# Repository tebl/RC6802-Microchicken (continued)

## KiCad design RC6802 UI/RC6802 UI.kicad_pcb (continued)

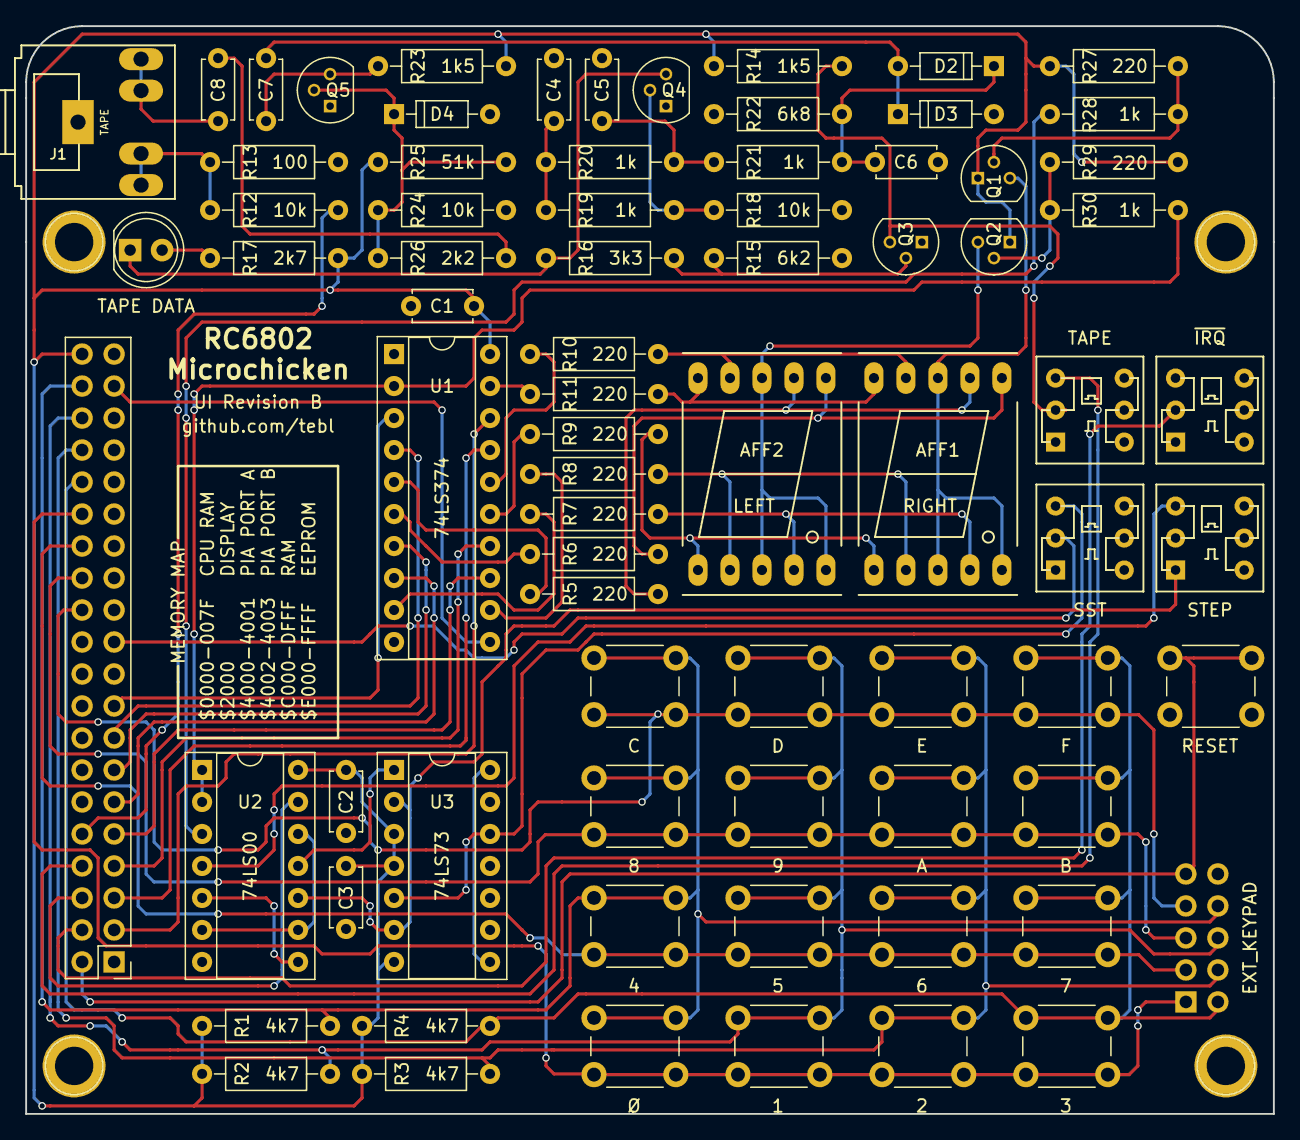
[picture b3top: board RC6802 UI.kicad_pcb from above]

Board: 2 copper layers, 99.1 x 86.4 mm, 80 parts (1 on the bottom side), 66 nets.

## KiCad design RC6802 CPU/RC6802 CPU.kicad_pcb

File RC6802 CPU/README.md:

# RC6802 Microchicken

One of my most enjoyable reads the past year has been "22 micro-computer projects - to build, learn and learn" by Daniel L. Metzger, the Microchicken-computer is described in detail within it and so I sought to build one myself. The computer has been designed as a set of smaller modules, for an overall description a listing of the available modules - see the main project [README](https://github.com/tebl/RC6802-Microchicken)!

## CPU
The CPU module has been designed to stack with the User Interface-module, doing it this way the overall project stays within manageable PCB-costs and should be buildable for anyone with a reasonable set of tools available. An assembled version of the CPU-module by itself as well as a version stacked underneath the User Interface module can be seen below.

The CPU board is actually a complete SBC (Single Board Computer) by itself, meaning that it can be used either standalone though you'd probably need to add some sort of additional hardware in order to see anything actually running. I hope to build more modules that can be used with it other than the standard User Interface. 

Some of the ICs however have been changed out with components that should be easier to source for a lot less money. For those that find themselves wondering why there are ICs with more capacity (RAM/ROM) than is actually available to the system, it's simply because they were cheaper than the smaller capacity variants and I didn't want to lay claim to more of the address space than what the original computer calls for (8K for each).

## Jumpers
| Reference | Position | Description                                        |
| --------- | -------- | -------------------------------------------------- |
| RAM_EN    | 1-2 *    | Enable on-chip 128 bytes of memory on 6802 CPU     |
|           | 2-3      | Disable on-chip memory or jumper if using 6808 CPU |
| RAM_SEL   | 1-2 *    | 8K of static RAM on addresses $C000-$DFFF          |
|           | 2-3      | 8k of static RAM on addresses $0000-$1FFF          |
| LED_EN    | 1-2 *    | Enable status LEDs                                 |
|           | 2-3      | Disable status LEDs                                |
| A14, A13  | 1-2 **   | EEPROM 8K window selection (sets line HIGH)        |
|           | 2-3 **   | EEPROM 8K window selection (sets line LOW)         |

*) Marks the default jumpered positions for a standalone RC6802 system with 6802 CPU installed.
**) A14 and A13 must be jumpered when using 28C256 EEPROM, leave unjumpered when using the lower capacity 28C64 EEPROM instead.

# Schematic
The supplied KiCad files should be sufficient as both a schematic and as a starting point for ordering PCBs (basically you could just zip the contents of the export folder and upload that on a fabrication site), the schematic is also available in [PDF-format](https://github.com/tebl/RC6802-Microchicken/raw/master/RC6802%20CPU/export/RC6802%20CPU.pdf) so that you print it out and hang it on your office wall, excellent conversation starter at any technology-oriented business worth working at (or so I keep telling myself)!

If you require more assistance, there is also a separate [Troubleshooting](https://github.com/tebl/RC6802-Microchicken/blob/master/Troubleshooting.md) guide as part of the supplied documentation. Also make sure to have a read through the [Manual](https://github.com/tebl/RC6802-Microchicken/blob/master/Manual.md) to see if it's a *feature* instead! Some of these documents may not actually exist at the time of clicking on them.

# BOM
This is the part list as it stands now, most should be easy to get a hold of from your local electronic component shop though you might have to consider other sources depending on the quality of your local vendor. Values in parenthesis are optional components that might not be needed (status LEDs and when using 28C256 EEPROMs).

Some vendors will have the same ICs in different form factors, the ones you want will often be specified as being in the form of a DIP/PDIP package - usually you'll want sockets for each of them as well. For the pin headers, you probably won't find the exact pin count so just buy the 40 pin versions and snip off the parts you don't need.

| Reference    | Item                                  | Count |
| ------------ | ------------------------------------- | ----- |
| PCB          | Fabricate yourself using Gerber files |     1 |
| C1-C8,C10    | 100nF ceramic capacitor               |     9 |
| C9,C11       | 22pF ceramic capacitor                |     2 |
| D1-D8        | 5mm LED (assorted colours)            |    (8)|
| J1           | 39p right angle pin header            |    (1)|
| J2           | 2x20 pin straight header              |     1 |
| J3           | 2.1mm x 5.5mm barrel plug             |     1 |
| J4,JP7-JP8   | Single row, 3 pin straight  header    |    (3)|
| JP2,JP3      | Single row, 3 pin straight  header    |     2 |
| R1-R4        | 3k3 (3300) ohm resistor               |     4 |
| R5-R12       | 220 ohm resistor                      |    (8)|
| U1           | MC6802 CPU (DIP-40) *                 |     1 |
| U2           | 62256 Static RAM (DIP-28)             |     1 |
| U3           | 28C64/28C256 EEPROM (DIP-28)          |     1 |
| U4           | 74LS00 (DIP-14)                       |     1 |
| U6           | MC6821 PIA (DIP-40)                   |     1 |
| U7           | 74LS138 (DIP-16)                      |     1 |
| U8           | 74LS240 (DIP-20)                      |    (1)|
| Y1           | 4Mhz crystal (HC-49)                  |     1 |
|              | Jumpers for settings (CAP headers)    |     5 |

*) You can also use an MC6808 processor, read jumpers descriptions on how to do this. The 6808 lacks the on-chip memory found on the 6802, so it needs to be jumpered as disabled with static memory moved into the lower addresses instead.

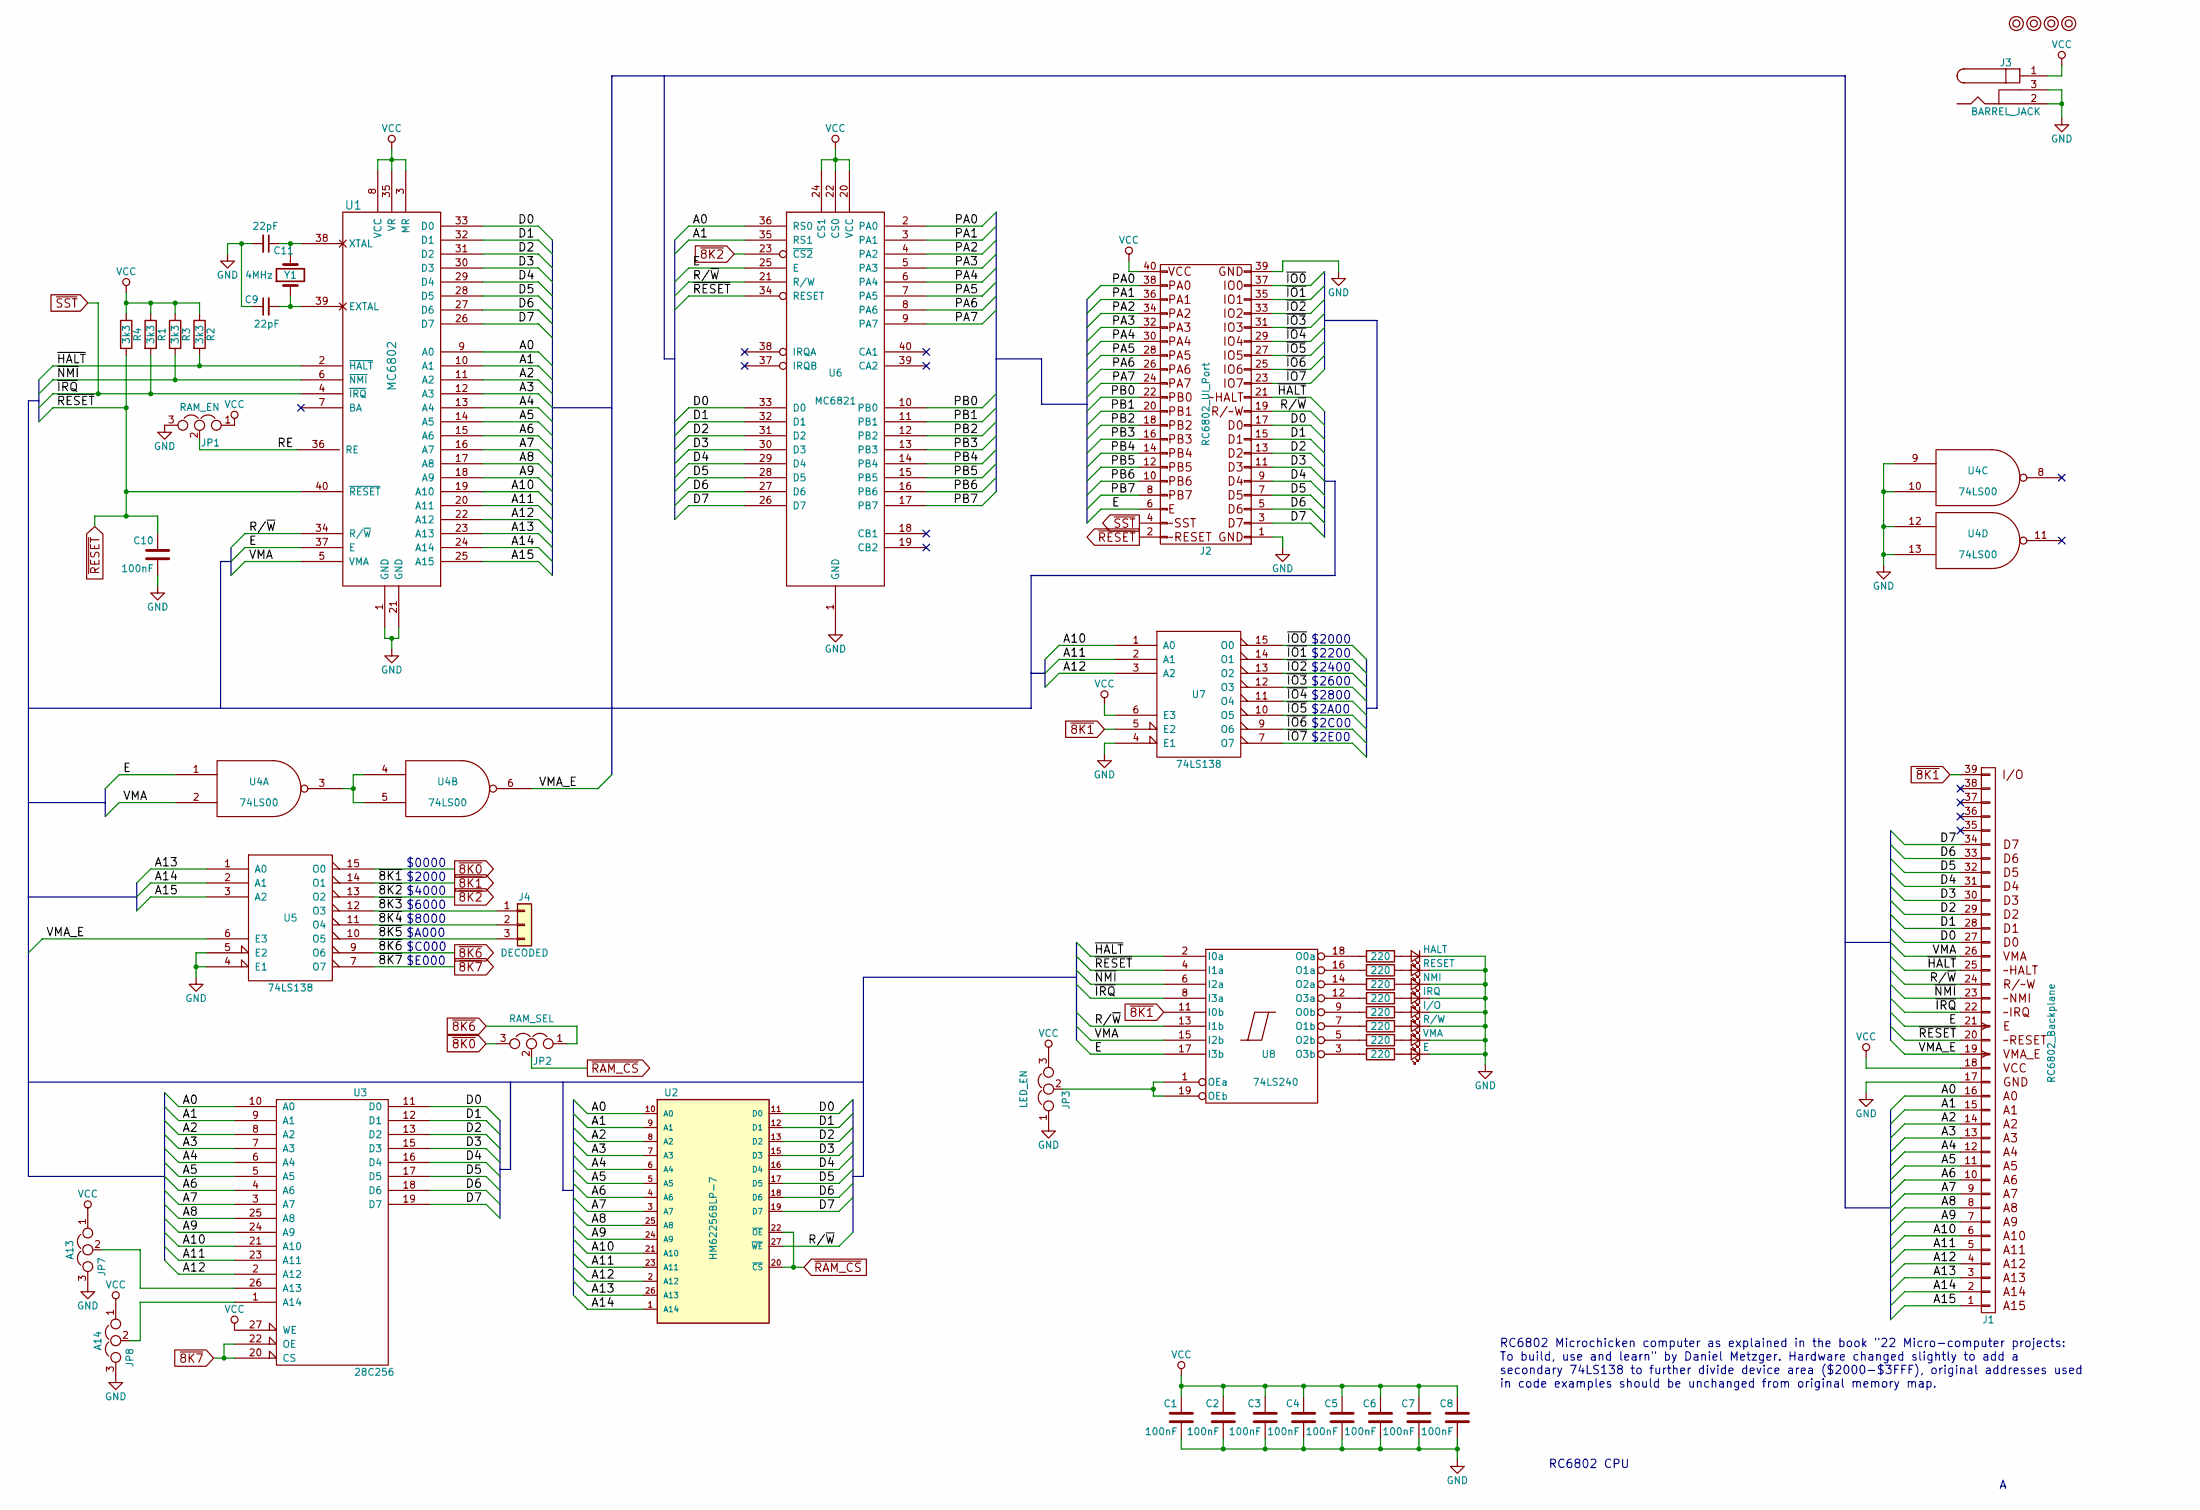
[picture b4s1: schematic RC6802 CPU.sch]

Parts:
C1, C2, C3, C4, C5, C6, C7, C8, C10: 100nF; C_Disc_D4.7mm_W2.5mm_P5.00mm
C9, C11: 22pF; C_Disc_D4.7mm_W2.5mm_P5.00mm
D1: HALT; LED_D5.0mm
D2: RESET; LED_D5.0mm
D3: NMI; LED_D5.0mm
D4: IRQ; LED_D5.0mm
D5: I/O; LED_D5.0mm
D6: R/W; LED_D5.0mm
D7: VMA; LED_D5.0mm
D8: E; LED_D5.0mm
J1: RC6802_Backplane; Pin_Header_Angled_1x39_Pitch2.54mm
J2: RC6802_UI_Port; Pin_Header_Straight_2x20_Pitch2.54mm
J3: BARREL_JACK
J4: DECODED; Pin_Header_Straight_1x03_Pitch2.54mm
JP1: RAM_EN; Pin_Header_Straight_1x03_Pitch2.54mm
JP2: RAM_SEL; Pin_Header_Straight_1x03_Pitch2.54mm
JP3: LED_EN; Pin_Header_Straight_1x03_Pitch2.54mm
JP7: A13; Pin_Header_Straight_1x03_Pitch2.54mm
JP8: A14; Pin_Header_Straight_1x03_Pitch2.54mm
M1, M2, M3, M4: Mounting; 1pin
R1, R2, R3, R4: 3k3; R_Axial_DIN0207_L6.3mm_D2.5mm_P10.16mm_Horizontal
R5, R6, R7, R8, R9, R10, R11, R12: 220; R_Axial_DIN0207_L6.3mm_D2.5mm_P7.62mm_Horizontal
U1: MC6802; DIP-40_W15.24mm_Socket
U2: HM62256BLP-7; DIP-28_W15.24mm_Socket
U3: 28C256; DIP-28_W15.24mm_Socket
U4: 74LS00; DIP-14_W7.62mm_Socket
U5, U7: 74LS138; DIP-16_W7.62mm_Socket
U6: MC6821; DIP-40_W15.24mm_Socket
U8: 74LS240; DIP-20_W7.62mm_Socket
Y1: 4MHz; Crystal_HC49-U_Vertical

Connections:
/A0: J1.16 (A0), U1.9 (A0), U2.10 (A0), U3.10 (A0), U6.36 (RS0)
/A1: J1.15 (A1), U1.10 (A1), U2.9 (A1), U3.9 (A1), U6.35 (RS1)
/A2: J1.14 (A2), U1.11 (A2), U2.8 (A2), U3.8 (A2)
/A3: J1.13 (A3), U1.12 (A3), U2.7 (A3), U3.7 (A3)
/A4: J1.12 (A4), U1.13 (A4), U2.6 (A4), U3.6 (A4)
/A5: J1.11 (A5), U1.14 (A5), U2.5 (A5), U3.5 (A5)
/A6: J1.10 (A6), U1.15 (A6), U2.4 (A6), U3.4 (A6)
/A7: J1.9 (A7), U1.16 (A7), U2.3 (A7), U3.3 (A7)
/A8: J1.8 (A8), U1.17 (A8), U2.25 (A8), U3.25 (A8)
/A9: J1.7 (A9), U1.18 (A9), U2.24 (A9), U3.24 (A9)
/A10: J1.6 (A10), U1.19 (A10), U2.21 (A10), U3.21 (A10), U7.1 (A0)
/A11: J1.5 (A11), U1.20 (A11), U2.23 (A11), U3.23 (A11), U7.2 (A1)
/A12: J1.4 (A12), U1.22 (A12), U2.2 (A12), U3.2 (A12), U7.3 (A2)
/A13: J1.3 (A13), U1.23 (A13), U2.26 (A13), U5.1 (A0)
/A14: J1.2 (A14), U1.24 (A14), U2.1 (A14), U5.2 (A1)
/A15: J1.1 (A15), U1.25 (A15), U5.3 (A2)
/D0: J1.27 (D0), J2.17, U1.33 (D0), U2.11 (D0), U3.11 (D0), U6.33 (D0)
/D1: J1.28 (D1), J2.15, U1.32 (D1), U2.12 (D1), U3.12 (D1), U6.32 (D1)
/D2: J1.29 (D2), J2.13, U1.31 (D2), U2.13 (D2), U3.13 (D2), U6.31 (D2)
/D3: J1.30 (D3), J2.11, U1.30 (D3), U2.15 (D3), U3.15 (D3), U6.30 (D3)
/D4: J1.31 (D4), J2.9, U1.29 (D4), U2.16 (D4), U3.16 (D4), U6.29 (D4)
/D5: J1.32 (D5), J2.7, U1.28 (D5), U2.17 (D5), U3.17 (D5), U6.28 (D5)
/D6: J1.33 (D6), J2.5, U1.27 (D6), U2.18 (D6), U3.18 (D6), U6.27 (D6)
/D7: J1.34 (D7), J2.3, U1.26 (D7), U2.19 (D7), U3.19 (D7), U6.26 (D7)
/E: J1.21 (PHI0), J2.6, U1.37 (E), U4.1, U6.25 (E), U8.17 (I3b)
/PA0: J2.38, U6.2 (PA0)
/PA1: J2.36, U6.3 (PA1)
/PA2: J2.34, U6.4 (PA2)
/PA3: J2.32, U6.5 (PA3)
/PA4: J2.30, U6.6 (PA4)
/PA5: J2.28, U6.7 (PA5)
/PA6: J2.26, U6.8 (PA6)
/PA7: J2.24, U6.9 (PA7)
/PB0: J2.22, U6.10 (PB0)
/PB1: J2.20, U6.11 (PB1)
/PB2: J2.18, U6.12 (PB2)
/PB3: J2.16, U6.13 (PB3)
/PB4: J2.14, U6.14 (PB4)
/PB5: J2.12, U6.15 (PB5)
/PB6: J2.10, U6.16 (PB6)
/PB7: J2.8, U6.17 (PB7)
/R/~W: J1.24 (RW), J2.19, U1.34 (R/~W), U2.27 (~WE), U6.21 (R/W), U8.13 (I1b)
/RE: JP1.2, U1.36 (RE)
/VMA: J1.26 (SYNC), U1.5 (VMA), U4.2, U8.15 (I2b)
/VMA_E: J1.19 (PHI2), U4.6, U5.6 (E3)
/~8K3: J4.1, U5.12 (O3)
/~8K4: J4.2, U5.11 (O4)
/~8K5: J4.3, U5.10 (O5)
/~HALT: J1.25 (READY), J2.21, R2.2, U1.2 (~HALT), U8.2 (I0a)
/~IO0: J2.37, U7.15 (O0)
/~IO1: J2.35, U7.14 (O1)
/~IO2: J2.33, U7.13 (O2)
/~IO3: J2.31, U7.12 (O3)
/~IO4: J2.29, U7.11 (O4)
/~IO5: J2.27, U7.10 (O5)
/~IO6: J2.25, U7.9 (O6)
/~IO7: J2.23, U7.7 (O7)
/~NMI: J1.23 (PHI1), R3.2, U1.6 (~NMI), U8.6 (I2a)
GND: C1.2, C2.2, C3.2, C4.2, C5.2, C6.2, C7.2, C8.2, C9.1, C10.2, C11.2, D1.1 (K), D2.1 (K), D3.1 (K), D4.1 (K), D5.1 (K), D6.1 (K), D7.1 (K), D8.1 (K), J1.17, J2.1, J2.39, J3.2, J3.3, JP1.3, JP3.1, JP7.3, JP8.3, U1.1 (GND), U1.21 (GND), U2.14 (GND), U3.14 (GND), U4.7 (GND), U4.9, U4.10, U4.12, U4.13, U5.4 (E1), U5.5 (E2), U5.8 (GND), U6.1 (GND), U7.4 (E1), U7.8 (GND), U8.10 (GND)
unnamed: C9.2, U1.39 (EXTAL), Y1.1
unnamed: C11.1, U1.38 (XTAL), Y1.2
unnamed: D1.2 (A), R8.1
unnamed: D2.2 (A), R7.1
unnamed: D3.2 (A), R6.1
unnamed: D4.2 (A), R5.1
unnamed: D5.2 (A), R12.1
unnamed: D6.2 (A), R11.1
unnamed: D7.2 (A), R10.1
unnamed: D8.2 (A), R9.1
unnamed: JP3.2, U8.1 (OEa), U8.19 (OEb)
unnamed: JP7.2, U3.26 (A13)
unnamed: JP8.2, U3.1 (A14)
unnamed: R5.2, U8.12 (O3a)
unnamed: R6.2, U8.14 (O2a)
unnamed: R7.2, U8.16 (O1a)
unnamed: R8.2, U8.18 (O0a)
unnamed: R9.2, U8.3 (O3b)
unnamed: R10.2, U8.5 (O2b)
unnamed: R11.2, U8.7 (O1b)
unnamed: R12.2, U8.9 (O0b)
unnamed: U4.3, U4.4, U4.5
VCC: C1.1, C2.1, C3.1, C4.1, C5.1, C6.1, C7.1, C8.1, J1.18, J2.40, J3.1, JP1.1, JP3.3, JP7.1, JP8.1, R1.1, R2.1, R3.1, R4.1, U1.3 (MR), U1.8 (VCC), U1.35 (VR), U2.28 (VCC), U3.27 (WE), U3.28 (VCC), U4.14 (VCC), U5.16 (VCC), U6.20 (VCC), U6.22 (CS0), U6.24 (CS1), U7.6 (E3), U7.16 (VCC), U8.20 (VCC)
~8K0: JP2.3, U5.15 (O0)
~8K1: J1.39, U5.14 (O1), U7.5 (E2), U8.11 (I0b)
~8K2: U5.13 (O2), U6.23 (~CS2)
~8K6: JP2.1, U5.9 (O6)
~8K7: U3.20 (CS), U3.22 (OE), U5.7 (O7)
~RAM_CS: JP2.2, U2.20 (~CS), U2.22 (~OE)
~RESET: C10.1, J1.20 (RESET), J2.2, R4.2, U1.40 (~RESET), U6.34 (RESET), U8.4 (I1a)
~SST: J1.22 (IRQ), J2.4, R1.2, U1.4 (~IRQ), U8.8 (I3a)

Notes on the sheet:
RC6802 CPU
$0000
$2000
$4000
$6000
$8000
$A000
$C000
$E000
RC6802 Microchicken computer as explained in the book "22 Micro-computer projects: To build, use and learn" by Daniel Metzger. Hardware changed slightly to add a secondary 74LS138 to further divide device area ($2000-$3FFF), original addresses used in code examples should be unchanged from original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
$2200
$2400
$2600
$2800
$2A00
$2C00
$2E00

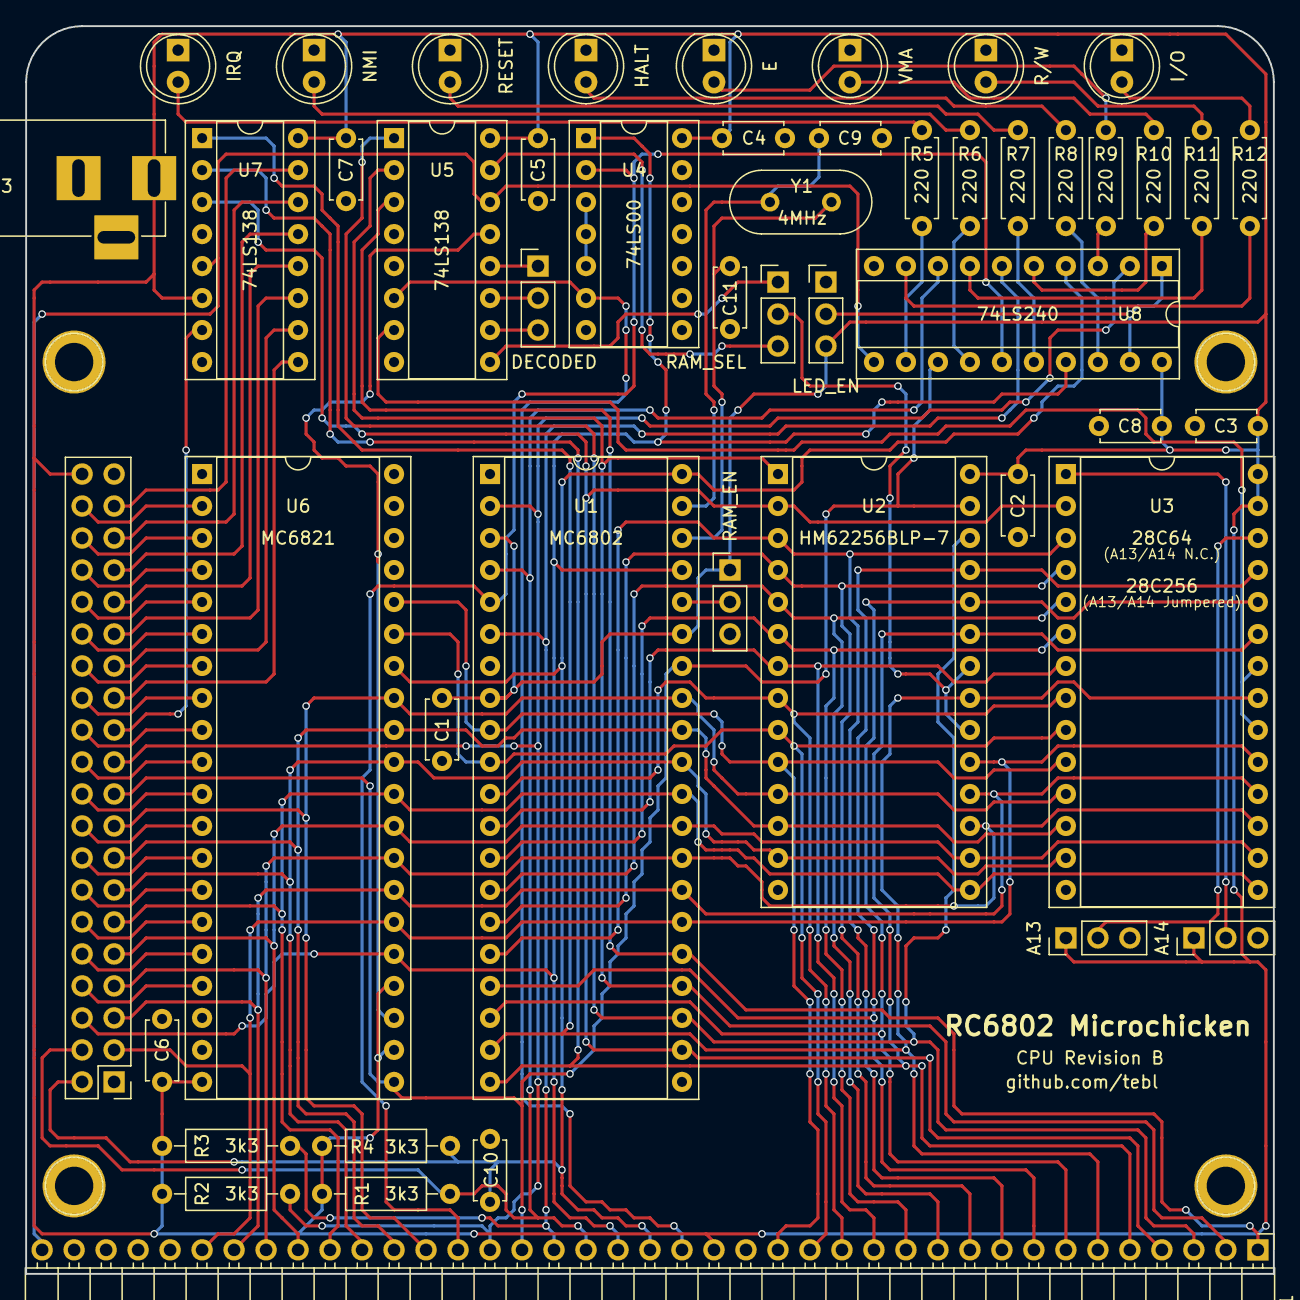
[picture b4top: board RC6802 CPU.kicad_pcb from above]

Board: 2 copper layers, 99.1 x 99.1 mm, 53 parts (0 on the bottom side), 90 nets.

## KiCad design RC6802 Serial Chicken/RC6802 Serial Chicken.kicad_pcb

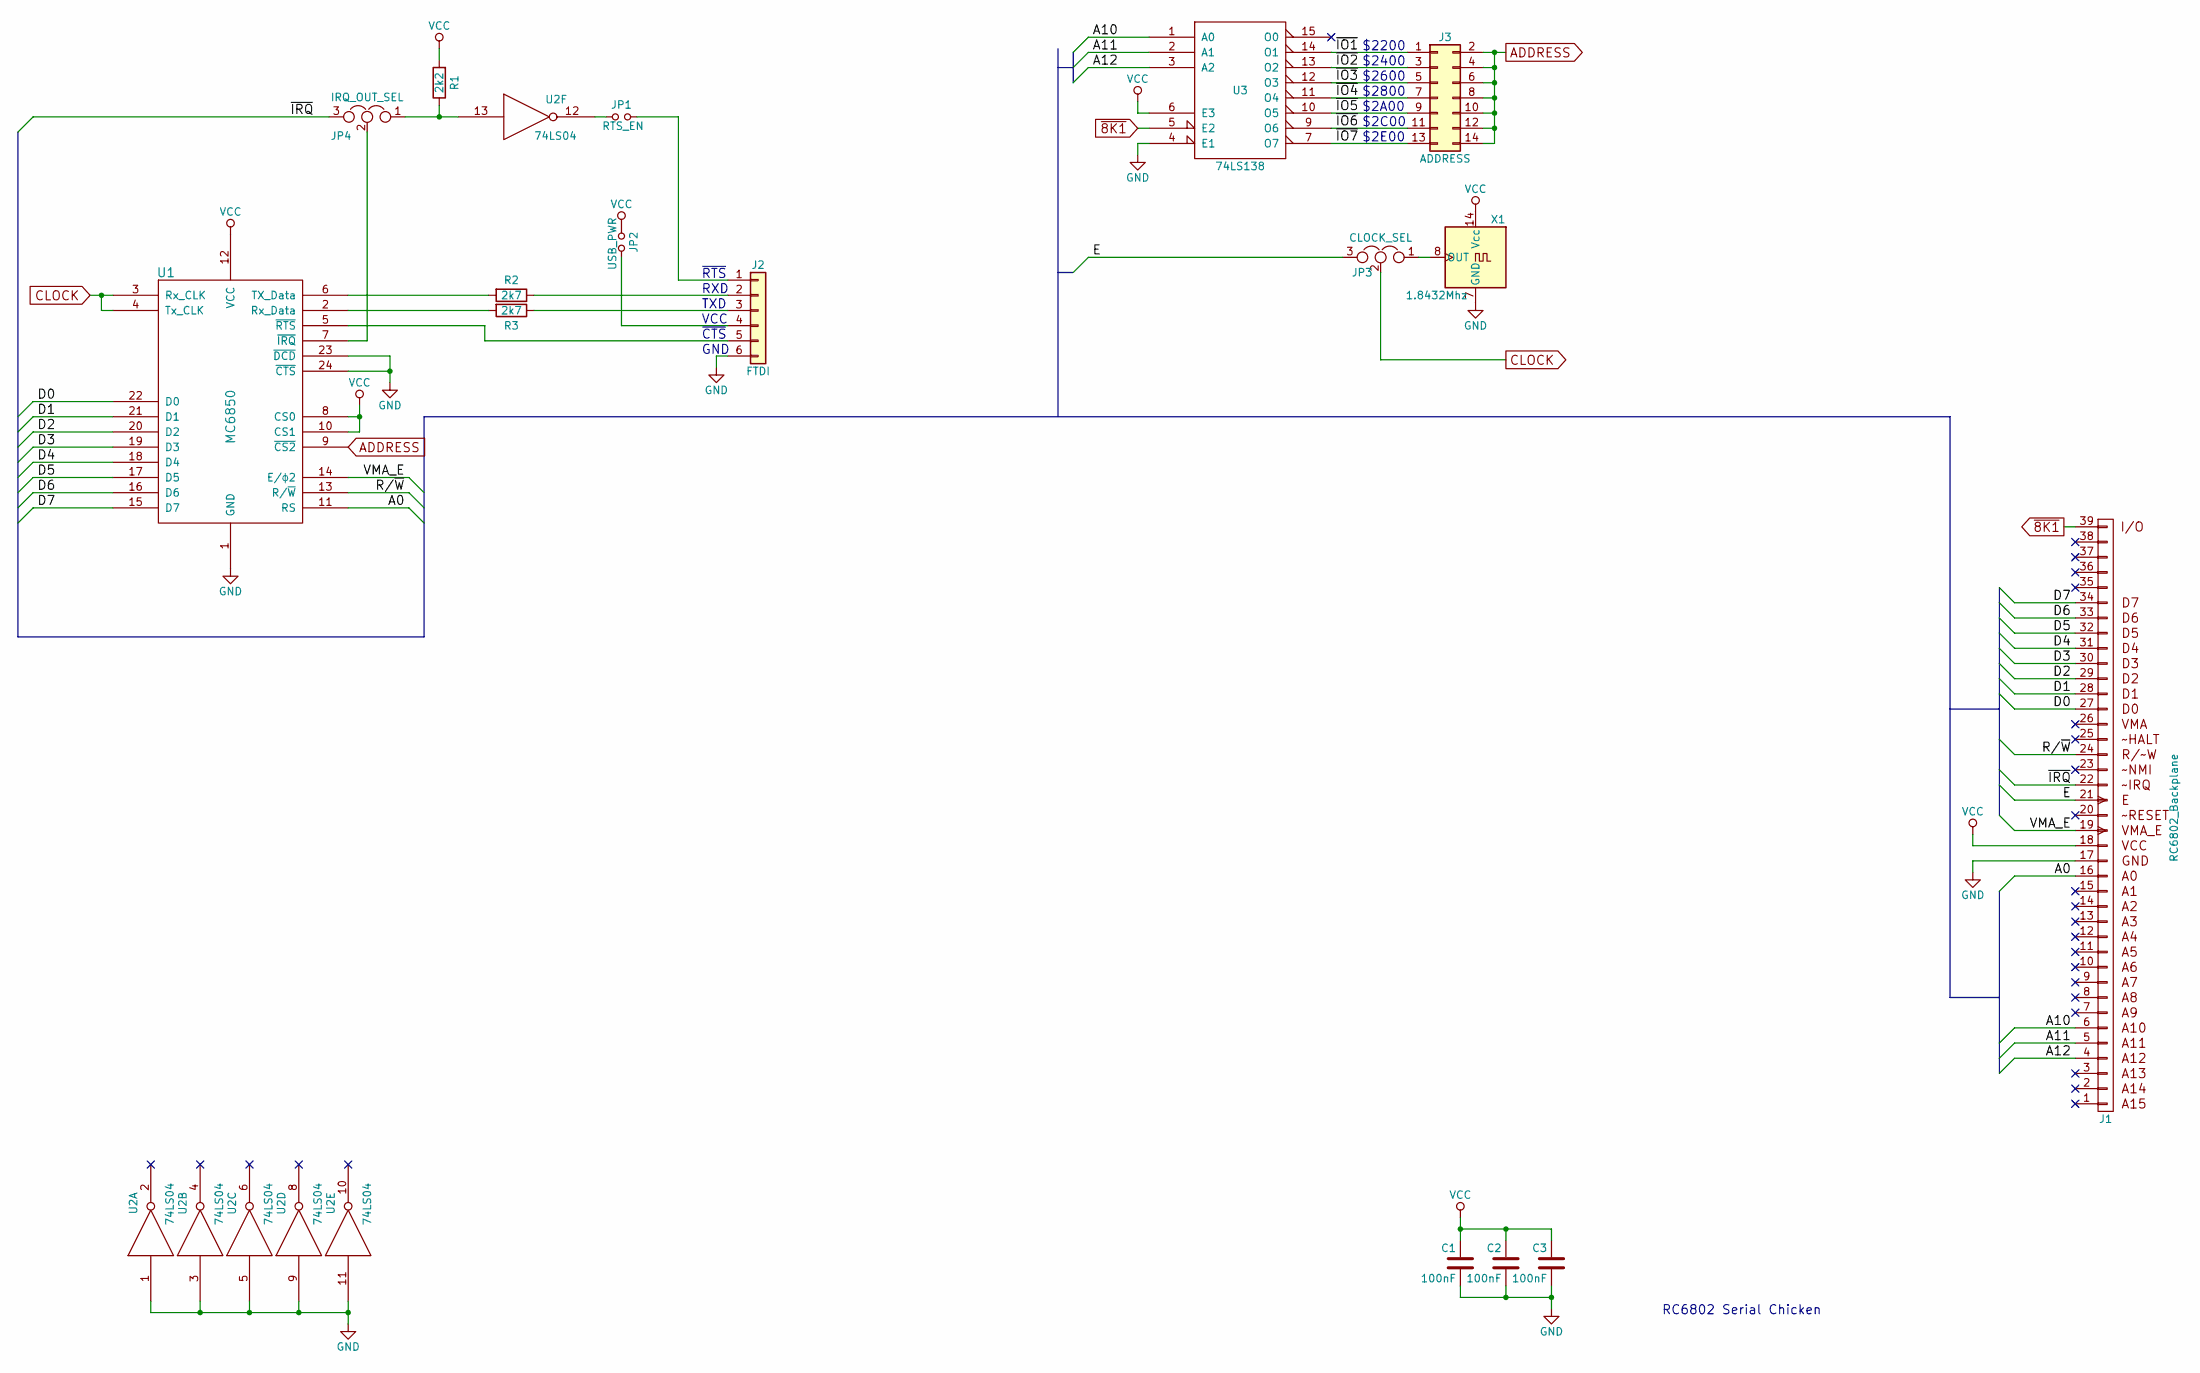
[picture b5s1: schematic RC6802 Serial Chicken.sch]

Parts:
C1, C2, C3: 100nF; C_Disc_D4.7mm_W2.5mm_P5.00mm
J1: RC6802_Backplane; Pin_Header_Angled_1x39_Pitch2.54mm
J2: FTDI; Pin_Header_Angled_1x06_Pitch2.54mm
J3: ADDRESS; Pin_Header_Straight_2x07_Pitch2.54mm
JP1: RTS_EN; Pin_Header_Straight_1x02_Pitch2.54mm
JP2: USB_PWR; Pin_Header_Straight_1x02_Pitch2.54mm
JP3: CLOCK_SEL; Pin_Header_Straight_1x03_Pitch2.54mm
JP4: IRQ_OUT_SEL; Pin_Header_Straight_1x03_Pitch2.54mm
R1: 2k2; R_Axial_DIN0207_L6.3mm_D2.5mm_P10.16mm_Horizontal
R2, R3: 2k7; R_Axial_DIN0207_L6.3mm_D2.5mm_P10.16mm_Horizontal
U1: MC6850; DIP-24_W15.24mm_Socket
U2: 74LS04; DIP-14_W7.62mm_Socket
U3: 74LS138; DIP-16_W7.62mm_Socket
X1: 1.8432Mhz; Oscillator_DIP-14

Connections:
/A0: J1.16 (A0), U1.11 (RS)
/A10: J1.6 (A10), U3.1 (A0)
/A11: J1.5 (A11), U3.2 (A1)
/A12: J1.4 (A12), U3.3 (A2)
/D0: J1.27 (D0), U1.22 (D0)
/D1: J1.28 (D1), U1.21 (D1)
/D2: J1.29 (D2), U1.20 (D2)
/D3: J1.30 (D3), U1.19 (D3)
/D4: J1.31 (D4), U1.18 (D4)
/D5: J1.32 (D5), U1.17 (D5)
/D6: J1.33 (D6), U1.16 (D6)
/D7: J1.34 (D7), U1.15 (D7)
/E: J1.21 (PHI0), JP3.3
/R/~W: J1.24 (RW), U1.13 (R/~W)
/VMA_E: J1.19 (PHI2), U1.14 (E/ϕ2)
/~IO1: J3.1, U3.14 (O1)
/~IO2: J3.3, U3.13 (O2)
/~IO3: J3.5, U3.12 (O3)
/~IO4: J3.7, U3.11 (O4)
/~IO5: J3.9, U3.10 (O5)
/~IO6: J3.11, U3.9 (O6)
/~IO7: J3.13, U3.7 (O7)
/~IRQ: J1.22 (IRQ), JP4.3
ADDRESS: J3.2, J3.4, J3.6, J3.8, J3.10, J3.12, J3.14, U1.9 (~CS2)
CLOCK: JP3.2, U1.3 (Rx_CLK), U1.4 (Tx_CLK)
GND: C1.2, C2.2, C3.2, J1.17, J2.6, U1.1 (GND), U1.23 (~DCD), U1.24 (~CTS), U2.1, U2.3, U2.5, U2.7 (GND), U2.9, U2.11, U3.4 (E1), U3.8 (GND), X1.7 (GND)
unnamed: J2.1, JP1.2
unnamed: J2.2, R2.1
unnamed: J2.3, R3.1
unnamed: J2.4, JP2.2
unnamed: J2.5, U1.5 (~RTS)
unnamed: JP1.1, U2.12
unnamed: JP3.1, X1.8 (OUT)
unnamed: JP4.1, R1.1, U2.13
unnamed: JP4.2, U1.7 (~IRQ)
unnamed: R2.2, U1.6 (TX_Data)
unnamed: R3.2, U1.2 (Rx_Data)
VCC: C1.1, C2.1, C3.1, J1.18, JP2.1, R1.2, U1.8 (CS0), U1.10 (CS1), U1.12 (VCC), U2.14 (VCC), U3.6 (E3), U3.16 (VCC), X1.14 (Vcc)
~8K1: J1.39, U3.5 (E2)

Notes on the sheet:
RC6802 Serial Chicken
$2200
$2400
$2600
$2800
$2A00
$2C00
$2E00
~RTS
RXD
TXD
VCC
~CTS
GND

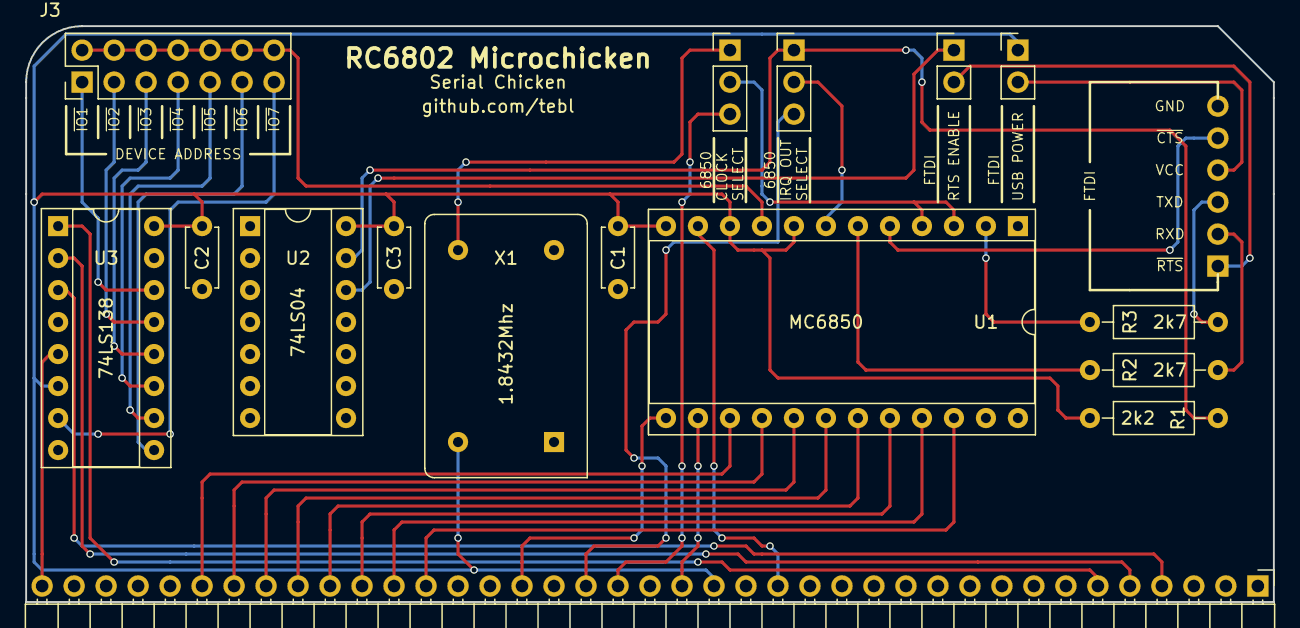
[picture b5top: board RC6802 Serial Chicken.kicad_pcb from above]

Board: 2 copper layers, 99.1 x 45.7 mm, 17 parts (1 on the bottom side), 39 nets.

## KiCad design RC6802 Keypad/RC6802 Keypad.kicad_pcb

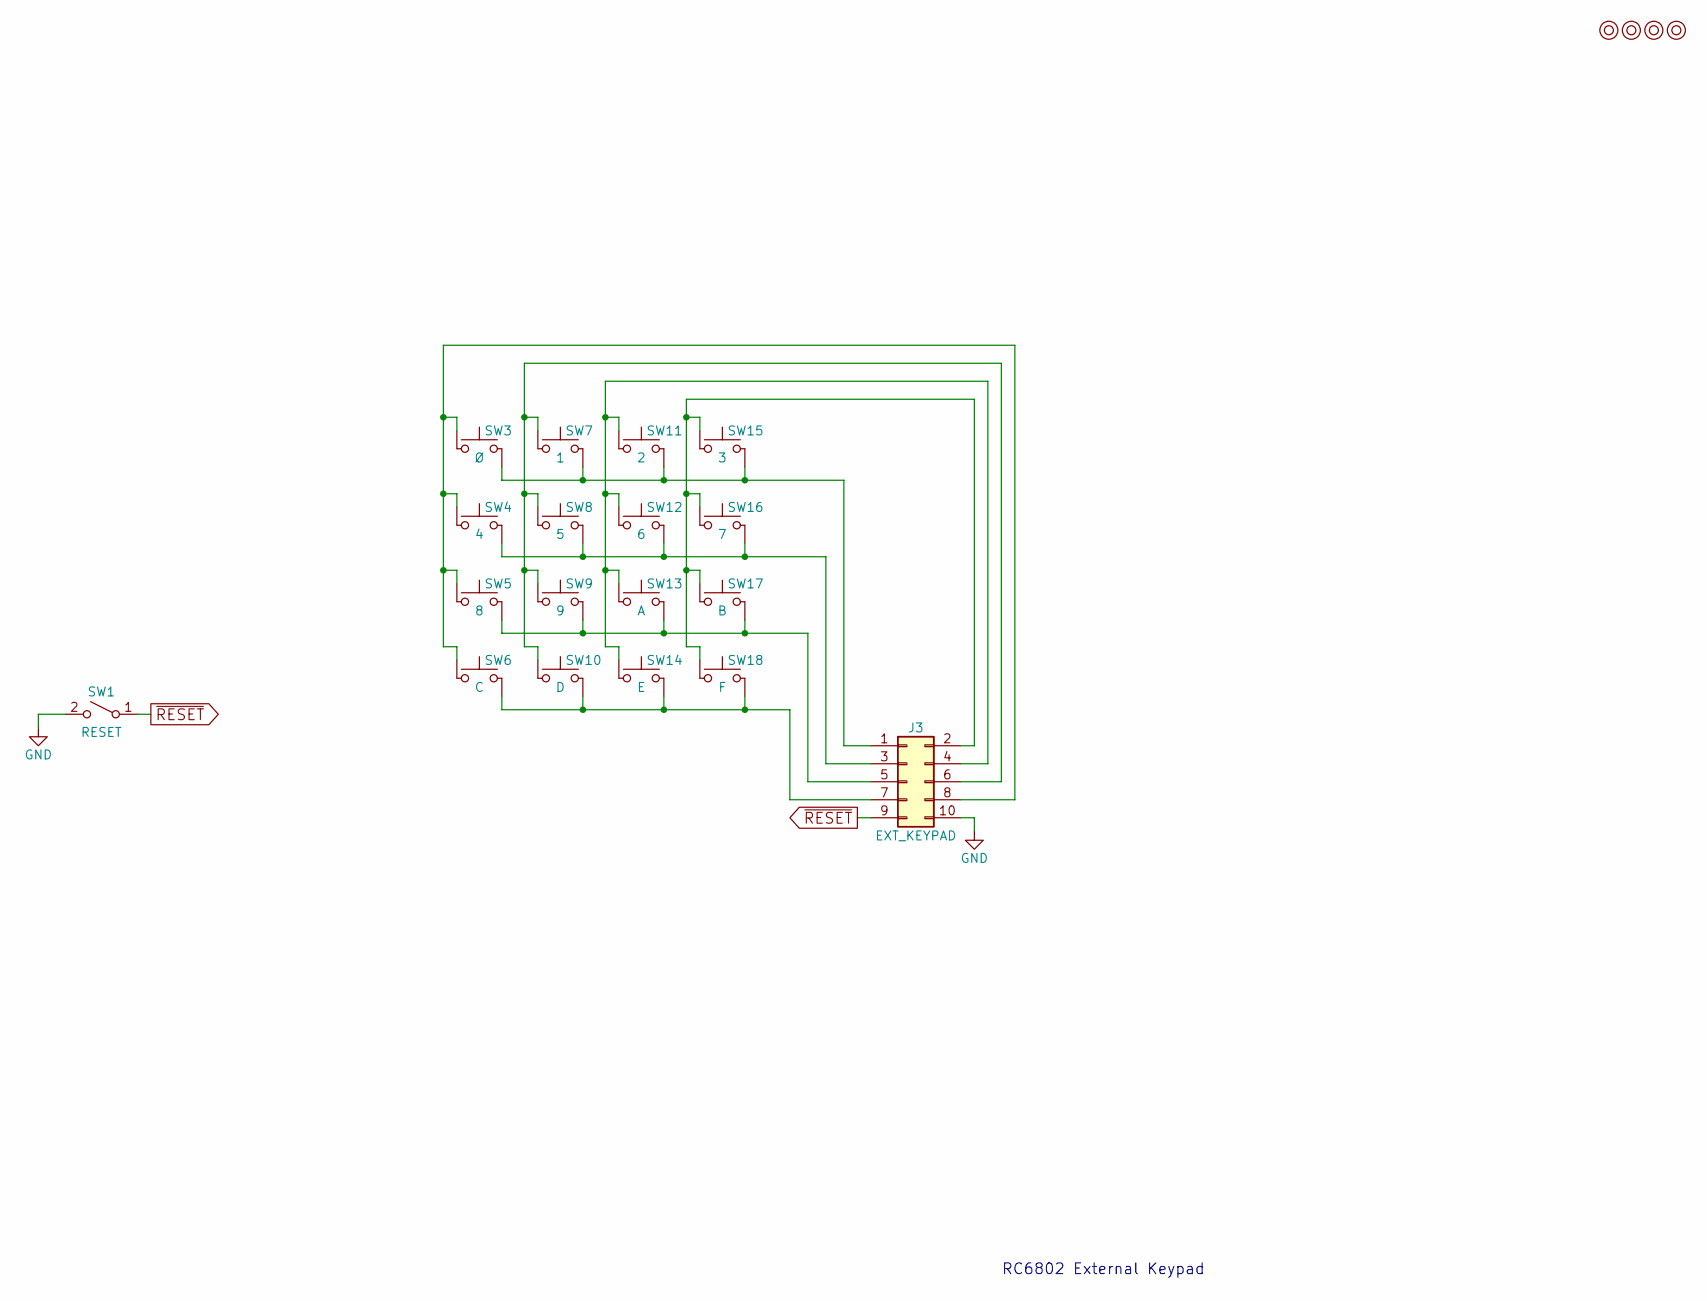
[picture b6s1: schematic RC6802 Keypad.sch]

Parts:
J3: EXT_KEYPAD; Pin_Header_Straight_2x05_Pitch2.54mm
M1, M2, M3, M4: Mounting; 1pin
SW1: RESET; SW_PUSH_6mm
SW3: Ø; SW_PUSH_6mm
SW4: 4; SW_PUSH_6mm
SW5: 8; SW_PUSH_6mm
SW6: C; SW_PUSH_6mm
SW7: 1; SW_PUSH_6mm
SW8: 5; SW_PUSH_6mm
SW9: 9; SW_PUSH_6mm
SW10: D; SW_PUSH_6mm
SW11: 2; SW_PUSH_6mm
SW12: 6; SW_PUSH_6mm
SW13: A; SW_PUSH_6mm
SW14: E; SW_PUSH_6mm
SW15: 3; SW_PUSH_6mm
SW16: 7; SW_PUSH_6mm
SW17: B; SW_PUSH_6mm
SW18: F; SW_PUSH_6mm

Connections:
GND: J3.10, SW1.2 (B)
unnamed: J3.1, SW3.2, SW7.2, SW11.2, SW15.2
unnamed: J3.2, SW15.1, SW16.1, SW17.1, SW18.1
unnamed: J3.3, SW4.2, SW8.2, SW12.2, SW16.2
unnamed: J3.4, SW11.1, SW12.1, SW13.1, SW14.1
unnamed: J3.5, SW5.2, SW9.2, SW13.2, SW17.2
unnamed: J3.6, SW7.1, SW8.1, SW9.1, SW10.1
unnamed: J3.7, SW6.2, SW10.2, SW14.2, SW18.2
unnamed: J3.8, SW3.1, SW4.1, SW5.1, SW6.1
~RESET: J3.9, SW1.1 (A)

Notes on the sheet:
RC6802 External Keypad

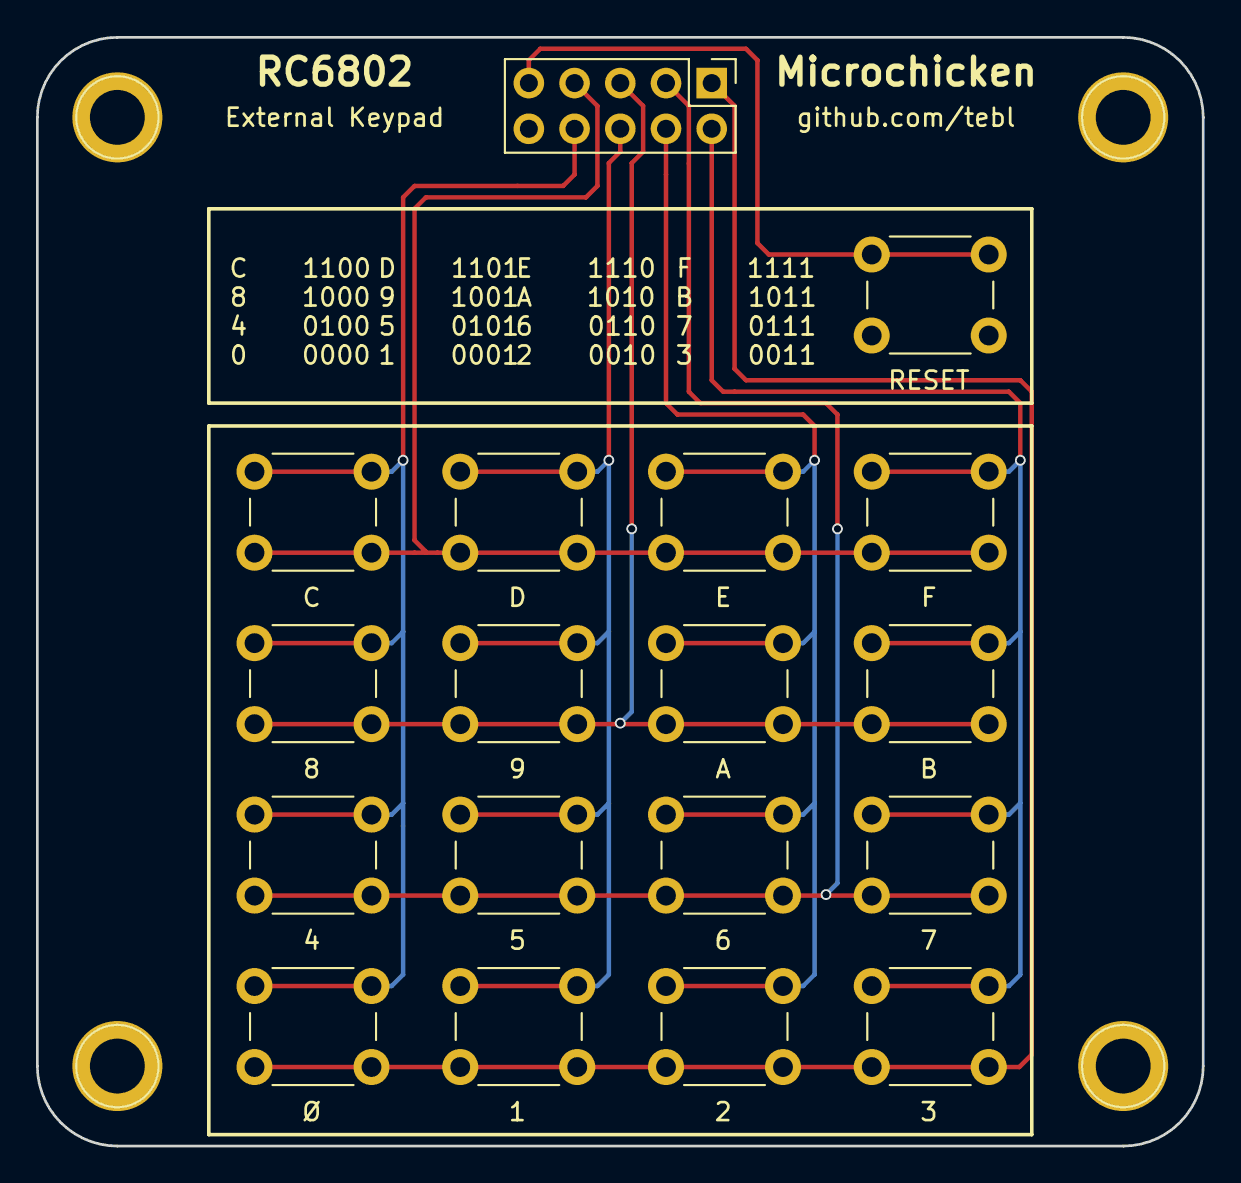
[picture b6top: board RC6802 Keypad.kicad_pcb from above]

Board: 2 copper layers, 64.8 x 61.6 mm, 22 parts (0 on the bottom side), 10 nets.

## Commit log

2019-09-18 CPU board schematic draft
2019-09-19 CPU board layout done
2019-09-19 UI board schematic draft
2019-09-20 Assigned 7segment and tape footprints
2019-09-21 UI board layout done
2019-09-21 Added LICENSE and README
2019-09-22 Added /VMA to backplane
2019-09-22 Added external keypad
2019-09-22 Added VMA_E signal to backplane
2019-09-22 Gerber export
2019-09-22 Serial chicken schematic
2019-11-10 Typed in monitor code
2019-11-10 Updated software
2019-11-13 Error in MC6802 footprint
2019-11-14 Added firmware documentation
2019-11-14 Fixed CPU bugs
2019-11-14 Updated UI to change footprints
2019-11-26 Revision B build
2019-11-26 CPU README
2019-11-26 UI README
2019-11-26 That example didn't work
2019-11-26 Added M3 standoff notes to UI
2019-11-27 Fixed silkscreen text
2019-11-27 UI silkscreen improved
2019-11-27 Order URLs added
2019-11-30 Schematic had wrong I/O addresses
2019-12-01 Beep chaser module
2019-12-01 Beep-chaser LED examples
2019-12-03 Latch beep chaser outputs on write only
2019-12-19 Added transistor to drive speaker
2019-12-20 IC-Tester schematic done
2019-12-20 IC-Tester layout
2020-01-07 PWR/SBY LEDs swapped
2020-01-09 firmware -> monitor
2020-01-09 IC-Tester original code
2020-01-09 Relocated data to add some space to ROM
2020-01-09 Updated with schematic changes from original
